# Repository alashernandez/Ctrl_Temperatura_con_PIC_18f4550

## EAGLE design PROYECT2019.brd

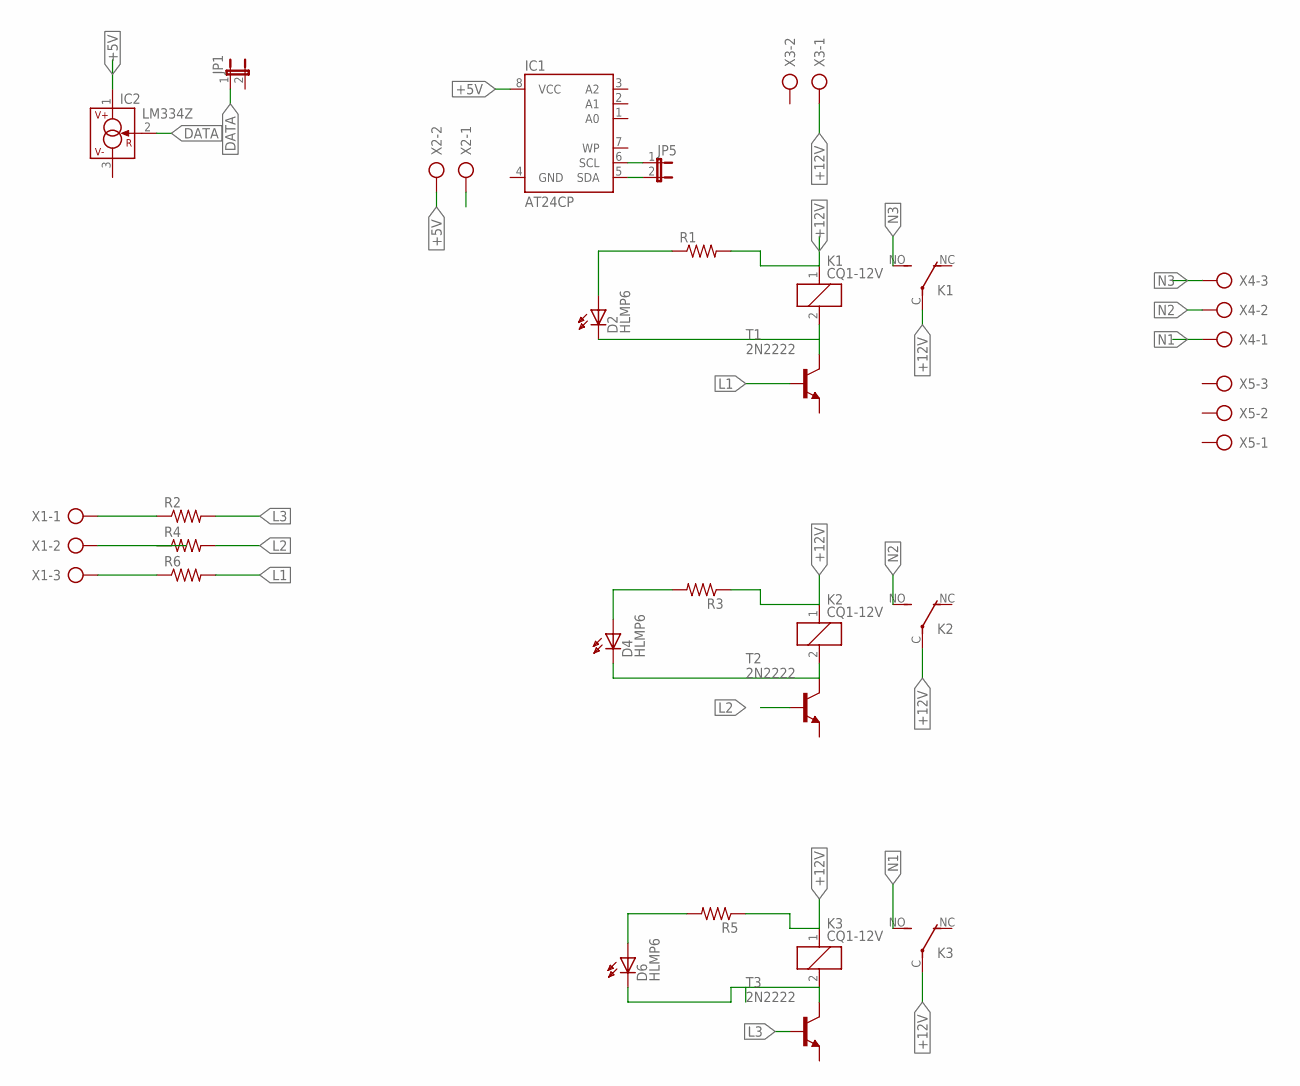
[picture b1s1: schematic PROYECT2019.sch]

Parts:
D2, D4, D6: HLMP6
IC1: AT24CP; DIL08
IC2: LM334Z; TO92
JP1, JP5: JP1E; JP1
K1, K2, K3: CQ1-12V; CQ1
R1, R2, R3, R4, R5, R6: R-US_0207/12; 0207/12
T1, T2, T3: 2N2222; TO18
X1, X4, X5: AK300/3
X2, X3: AK300/2

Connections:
+5V: IC1.8 (VCC), IC2.1 (V+), X2.2
+12V: K1.1, K1.C, K2.1, K2.C, K3.1, K3.C, R1.2, R3.1, R5.1, X3.1
DATA: IC2.2 (R), JP1.1
GND: IC1.4 (GND)
L1: R6.2, T1.2 (B)
L2: R4.2, T2.2 (B)
L3: R2.2, T3.2 (B)
N1: K3.NO (S), X4.1
N2: K2.NO (S), X4.2
N3: K1.NO (S), X4.3
unnamed: R2.1, X1.1
unnamed: R4.1, X1.2
unnamed: R6.1, X1.3
unnamed: D2.A, R1.1
unnamed: D2.K, K1.2, T1.3 (C)
unnamed: D4.A, R3.2
unnamed: D6.A, R5.2
unnamed: D4.K, K2.2, T2.3 (C)
unnamed: D6.K, K3.2, T3.3 (C)
unnamed: IC1.6 (SCL), JP5.1
unnamed: IC1.5 (SDA), JP5.2

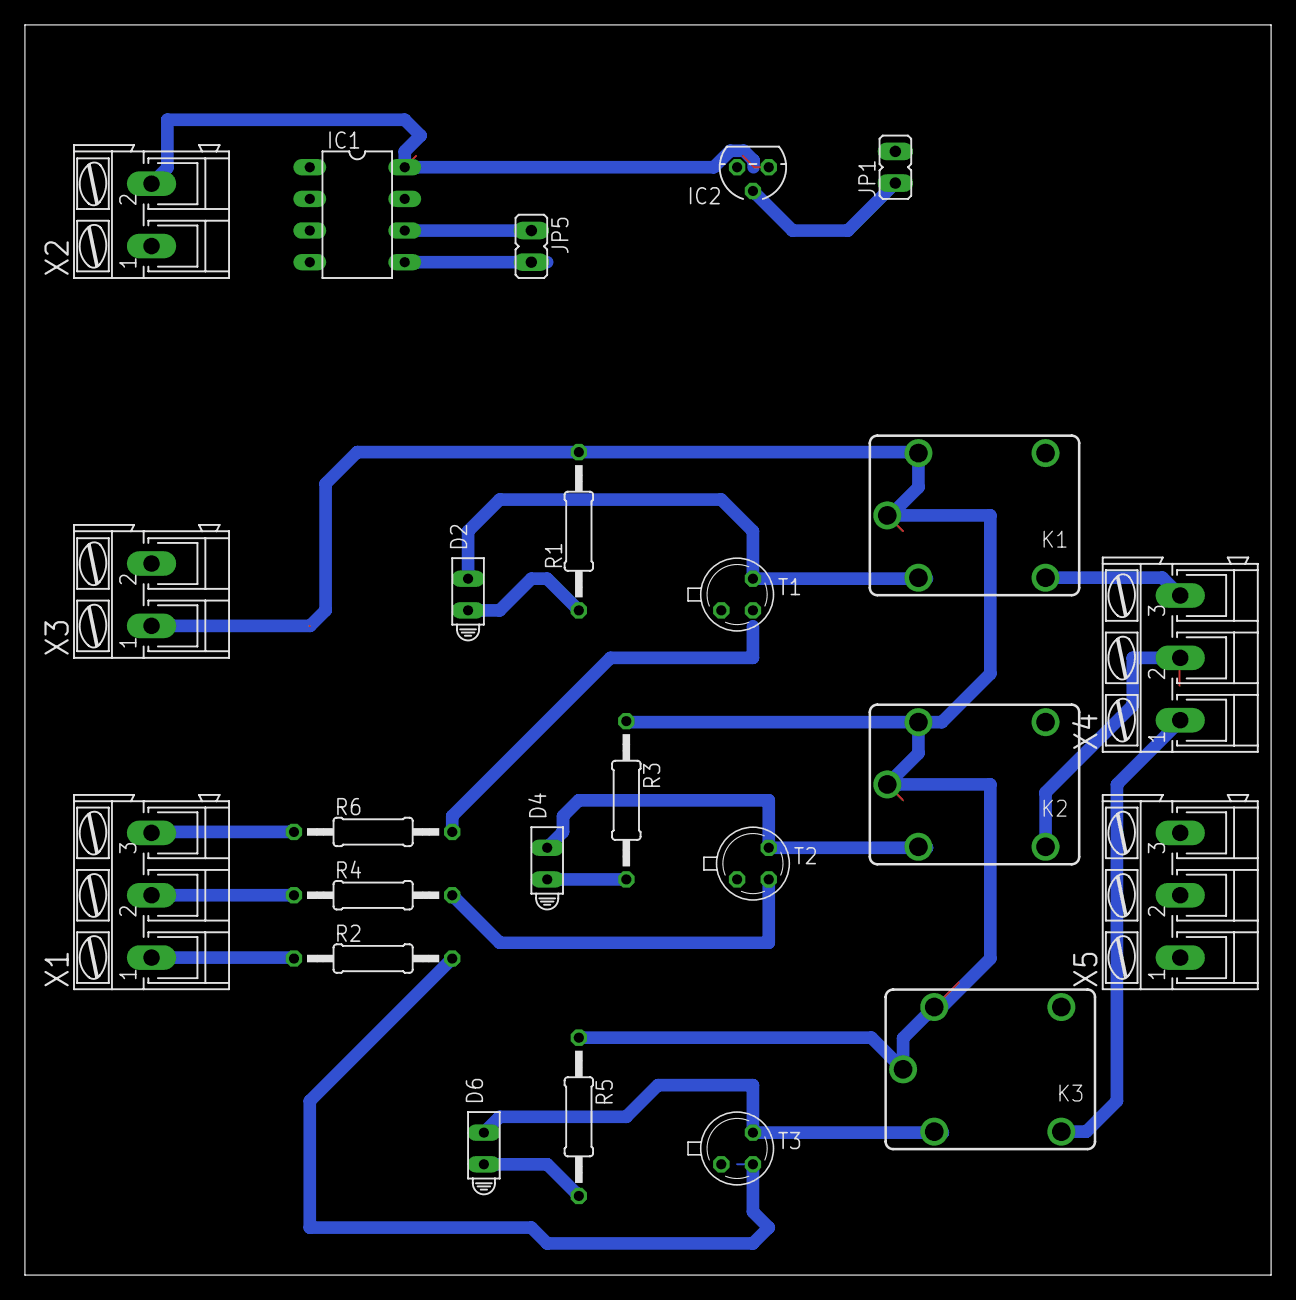
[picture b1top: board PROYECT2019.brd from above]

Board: 2 copper layers, 100.0 x 100.3 mm, 24 parts (0 on the bottom side), 20 nets.
